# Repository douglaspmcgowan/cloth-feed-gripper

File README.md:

# Cloth-feed gripper site

Public site for the cloth-feed gripper, a UC Berkeley ME102B design that has not been built. It has a landing page, the film, and the interactive design review app. Everything is static and served from `public/`.

## What is in `public/`

| Path | Source |
|---|---|
| `index.html`, `landing.css`, `landing.js`, `favicon.svg` | hand-written, no framework or build |
| `review/index.html` | the review app, wrapped in a document head and a Home link; generated |
| `media/` | teaser, full film, vertical cut, posters and the social image; generated |
| `licenses/` | licence texts for the third-party assets; generated |
| `facts.json`, `tokens.css`, `provenance.json` | figures, design tokens and file hashes read from the source; generated |

`scripts/sync.py` writes every generated file from the source repository at one commit. `provenance.json` records the source repository name, that commit, the sync date, and each served file's public path, sha256 and size; it says nothing about the source repository's layout. The landing page shows no figure that is not read from `facts.json`.

## Commands

```powershell
npm ci
npx playwright install chromium

python scripts/sync.py --ref 996dce6      # refresh generated files; running it twice changes nothing
python scripts/check_public.py            # scan public/ for private content
npm run serve                             # http://127.0.0.1:4173/
npm test                                  # Playwright, 3 sizes x light and dark
npm run lint
```

The moved CAD, analysis, electronics and firmware checks use Python 3.12 and the
dependencies in `requirements-dev.txt`. For example, run
`uv run --python 3.12 --no-project --with-requirements requirements-dev.txt python -m pytest -q cad/gripper analysis/gripper docs/gripper/test ecad/gripper firmware/gripper/test`
from this repository's root. Some committed analysis outputs are already stale;
the move does not regenerate their computed values.

`sync.py` reads this repository by default and takes `--source <path to a checkout>` when another checkout is needed. `.sync/state.json` is git-ignored, so the first run in a fresh clone has no record of the last sync and may rebuild every generated file; the result is the same bytes.

## Checks

- `scripts/check_public.py` looks for emails, phones, addresses, student IDs, local paths, credential shapes, names of people, handout-style phrases and paths from the source repository (read from `scripts/sync.py`'s own input table), in every file including the text inside the review app, and for any digit typed into the landing page's text. A hit passes only with a reviewed line in `scripts/public-allowlist.txt` that also states how many times it occurs; a different count fails. `--self-test` plants one hit per rule. A shingle comparison against a course handout runs only with `--handout <file>` and has not been run. Two limits: the source-path rule knows only the paths `sync.py` reads, so the review app's other evidence citations (relative file names in its Sources panels, which point into the private design repository and are kept on purpose) are not counted; and the typed-digit rule covers the landing page's static text, not text a script writes.
- `npm test` covers console errors, sideways scroll, broken text, the hero poster, film playback, the 3D canvas, each landing door, the Home link, and that nothing outside `public/` is served.

## Deploying

`vercel.json` sets `public` as the output directory with no framework and no build command. Deploying is a separate step that needs the owner's say-so.

After a deploy, run the guard against the live address:

```powershell
npm run check:live -- https://cloth-feed-gripper.vercel.app
```

It prints one line per path and ends with `check_live: N ok, M failed`. It exits non-zero unless the landing page, `/review/`, `/facts.json`, the full film (HEAD) and a licence text return 200, the landing page carries its title and `/facts.json` parses with a requirement count, and every path in its hidden list returns 404. The hidden list is in `scripts/check_live.mjs`: repository files outside `public/` (contract, task and spec files, `package.json`, `vercel.json`, `.git/config`, `.sync/state.json`, the scripts, the allowlist, a test, `node_modules`) and `public/`-prefixed copies of served files.

## Runtime dependencies

The review app loads three.js from jsDelivr, and both pages load Public Sans from Google Fonts. Without a network the 3D views do not draw.

## Credits

See the credits section of the landing page: SO-ARM100 geometry (Apache-2.0), Archivo and Public Sans (OFL), three.js (MIT).

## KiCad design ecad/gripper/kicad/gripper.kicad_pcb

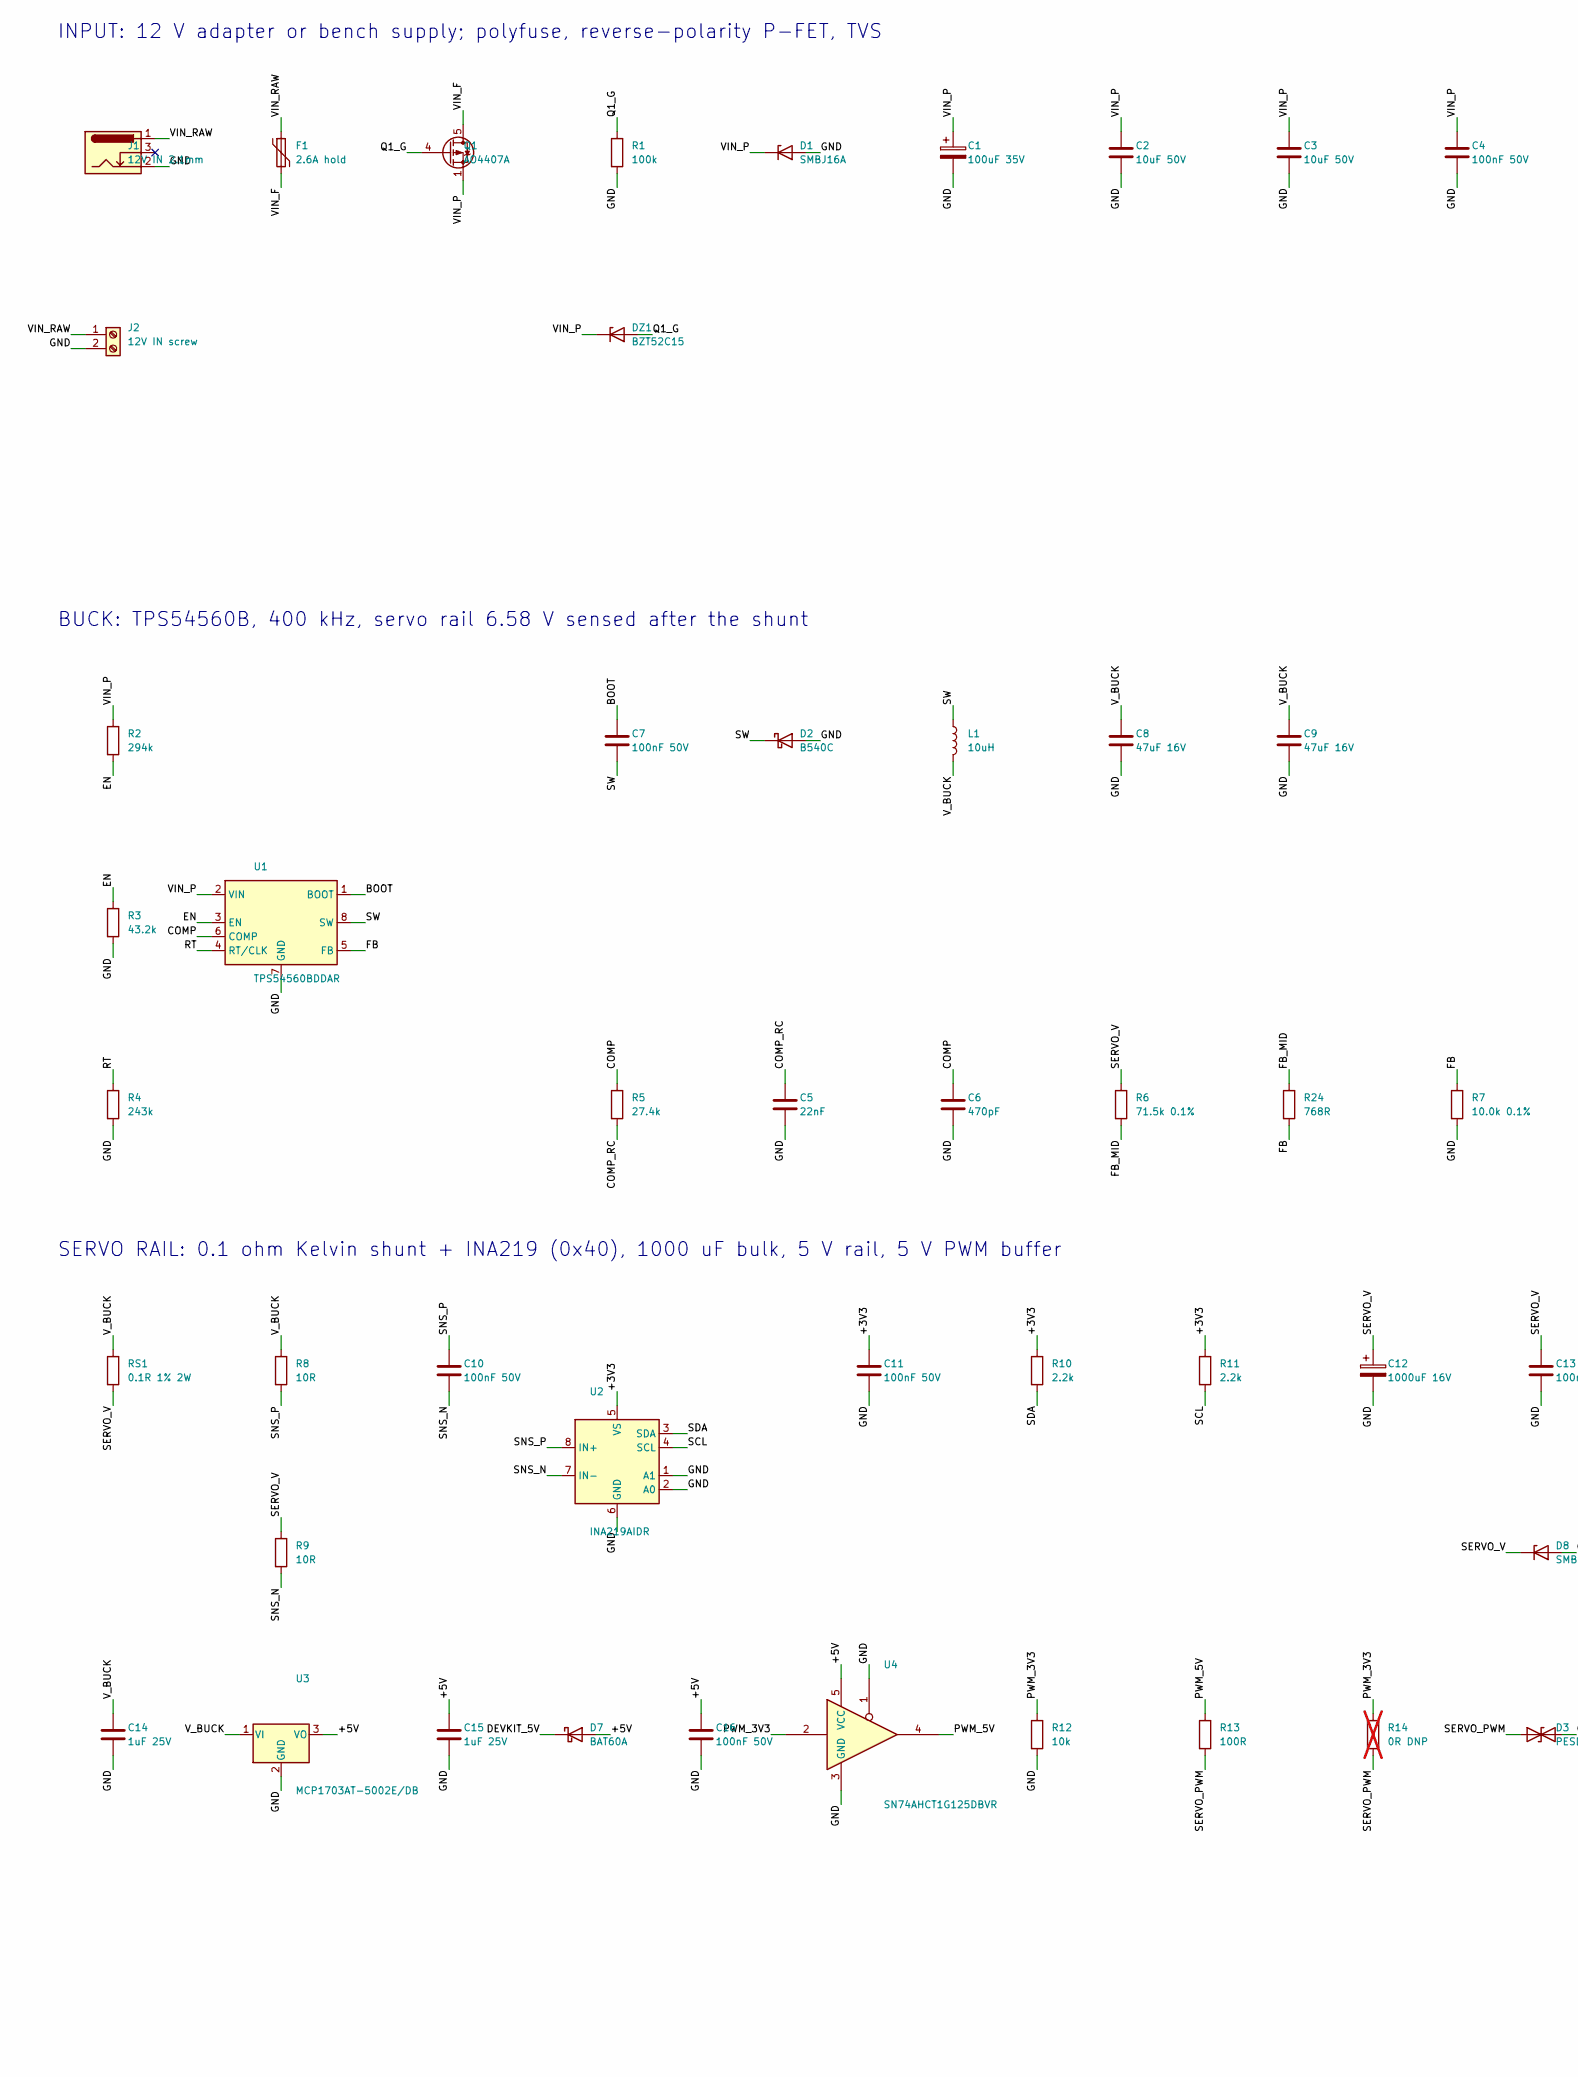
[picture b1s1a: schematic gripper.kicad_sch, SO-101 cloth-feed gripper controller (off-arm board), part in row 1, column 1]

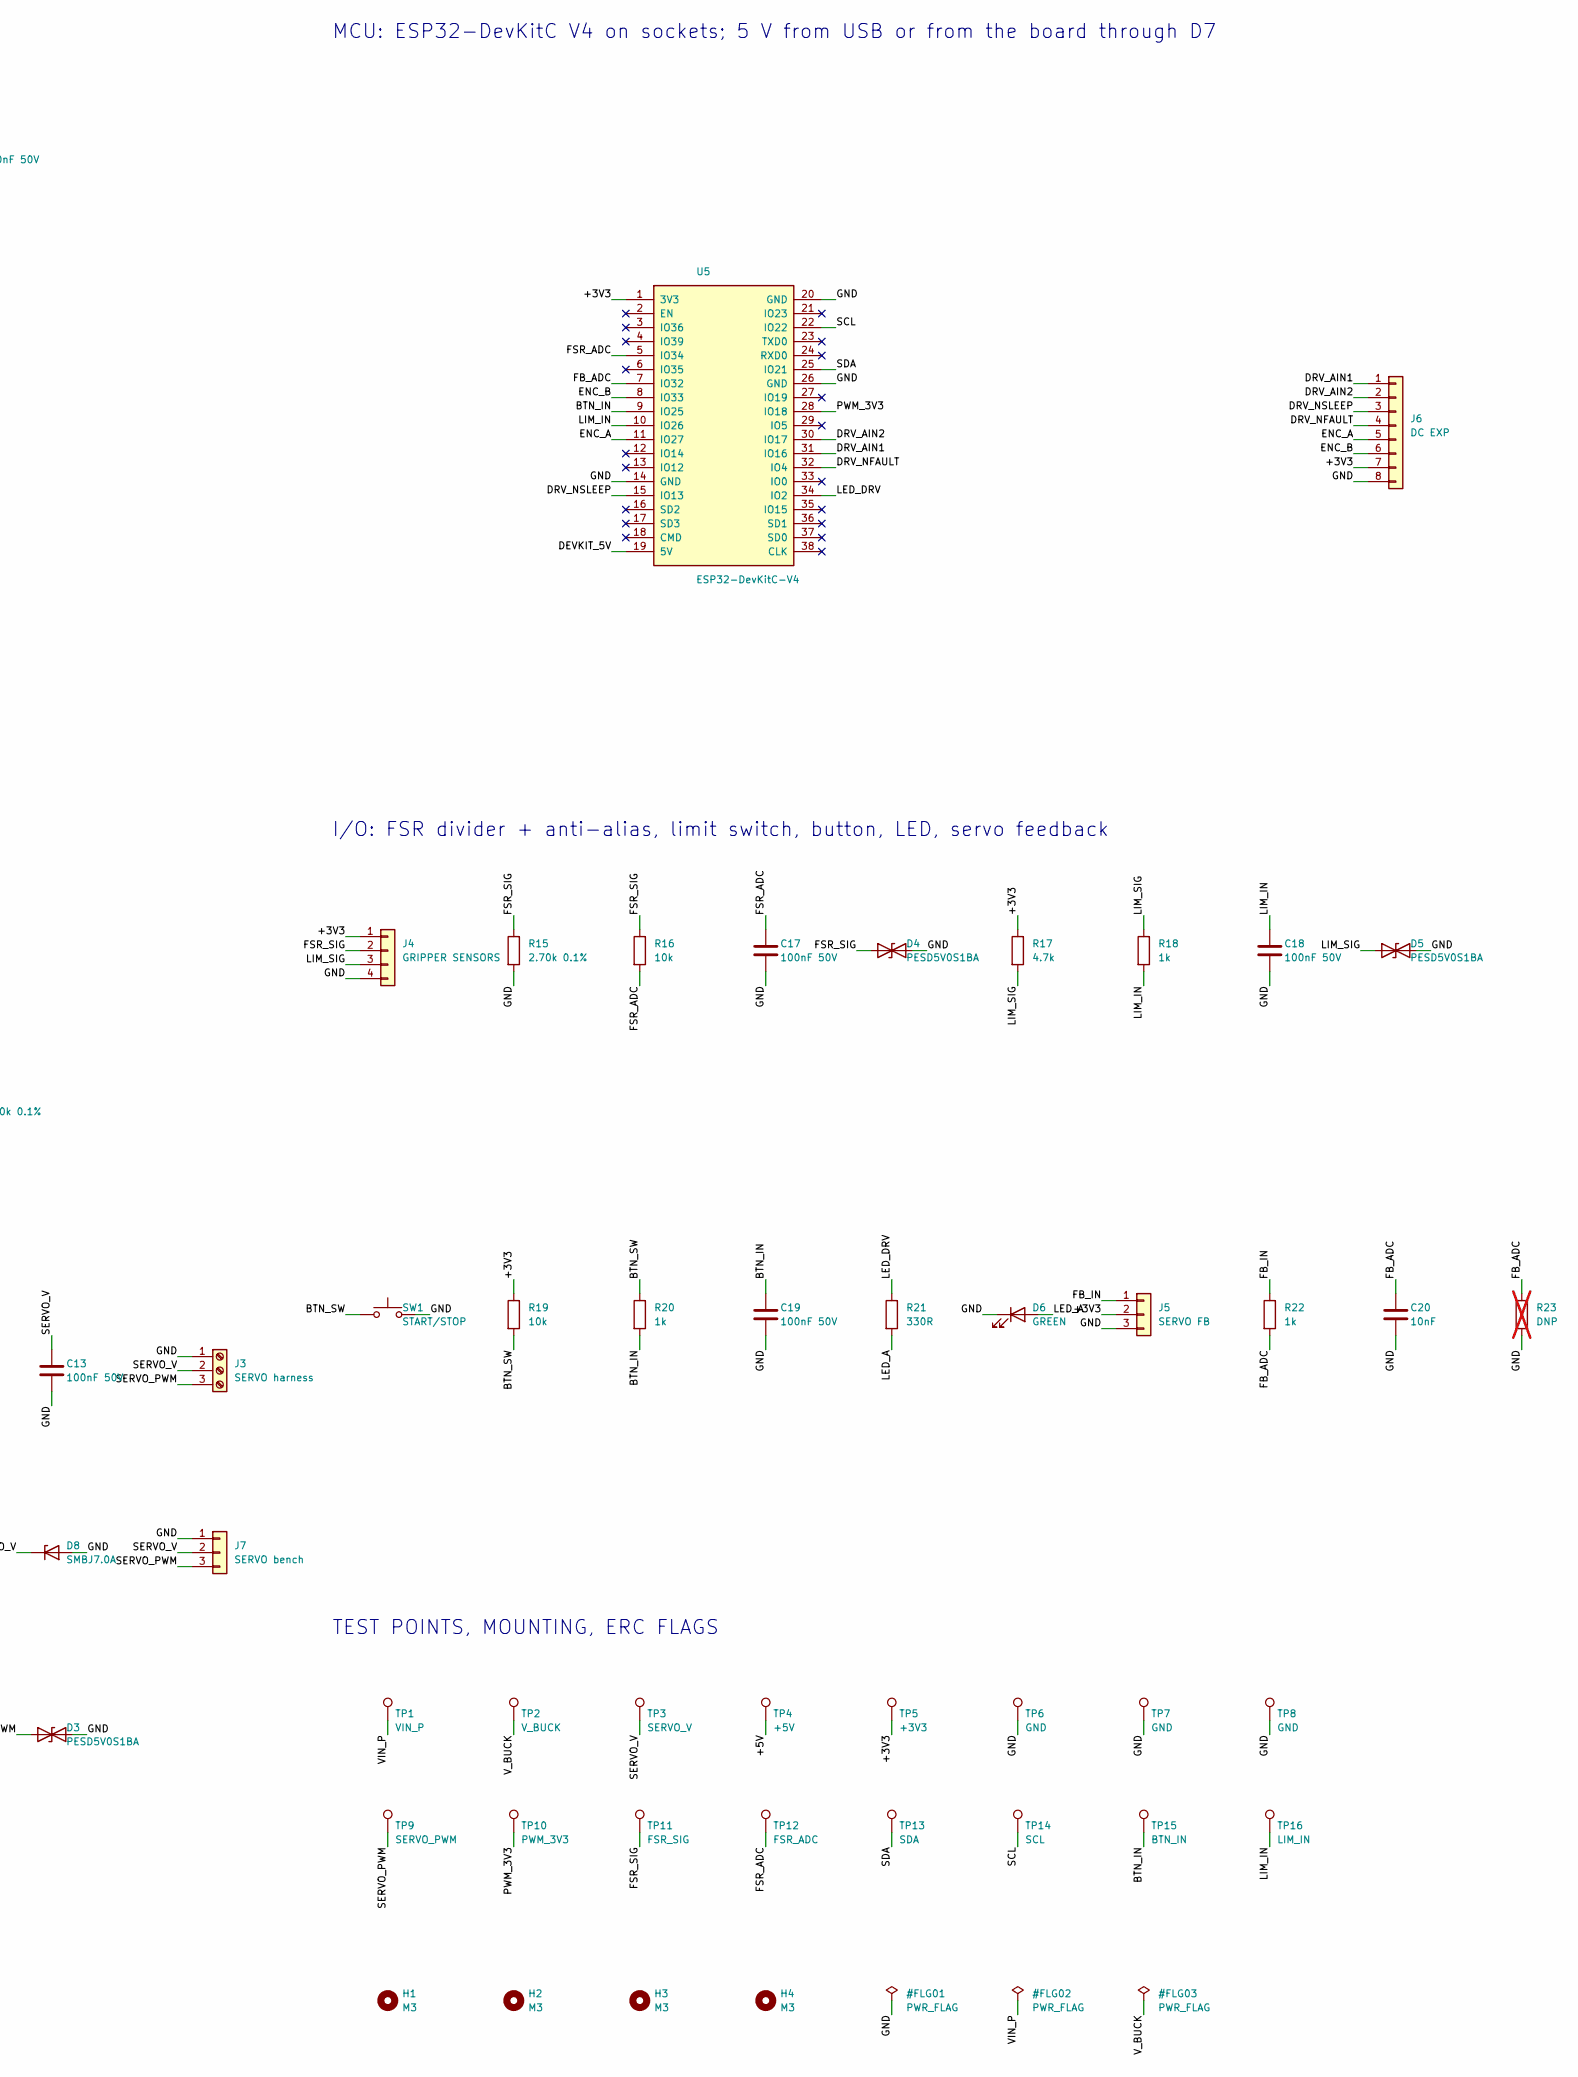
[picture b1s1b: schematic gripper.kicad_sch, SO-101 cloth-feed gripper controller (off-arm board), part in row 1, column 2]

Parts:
C1: 100uF 35V; CP_Radial_D8.0mm_P3.50mm; MPN EEU-FR1V101
C2, C3: 10uF 50V; C_1210_3225Metric; MPN GRM32ER71H106KA12L; LCSC Part # C77102
C4, C7, C10, C11, C13, C16, C17, C18, C19: 100nF 50V; C_0603_1608Metric; MPN CC0603KRX7R9BB104; LCSC Part # C14663
C5: 22nF; C_0603_1608Metric; MPN CL10B223KB8NNNC; LCSC Part # C21122
C6: 470pF; C_0603_1608Metric; MPN CL10C471JB8NNNC; LCSC Part # C27694
C8, C9: 47uF 16V; C_1210_3225Metric; MPN CL32A476KOJNNWE; LCSC Part # C730498
C12: 1000uF 16V; CP_Radial_D10.0mm_P5.00mm; MPN EEU-FR1C102B
C14, C15: 1uF 25V; C_0603_1608Metric; MPN CL10A105KB8NNNC; LCSC Part # C15849
C20: 10nF; C_0603_1608Metric; MPN CL10B103KB8NNNC; LCSC Part # C1589
D1: SMBJ16A; D_SMB; MPN SMBJ16A-M3/52; LCSC Part # C1979375
D2: B540C; D_SMC; MPN B540C-13-F; LCSC Part # C72264
D3, D4, D5: PESD5V0S1BA; D_SOD-323; MPN PESD5V0S1BA,115; LCSC Part # C19224
D6: GREEN; LED_0805_2012Metric; MPN TJ-S2012SW8TGLC2G-A5; LCSC Part # C192319
D7: BAT60A; D_SOD-323; MPN BAT60AE6327HTSA1
D8: SMBJ7.0A; D_SMB; MPN SMBJ7.0A
DZ1: BZT52C15; D_SOD-123; MPN BZT52C15; LCSC Part # C2104
F1: 2.6A hold; Fuse_1812_4532Metric; MPN SMD1812P260TF/16; LCSC Part # C20814
H1, H2, H3, H4: M3; MountingHole_3.2mm_M3
J1: 12V IN 2.1mm; BarrelJack_CUI_PJ-102AH_Horizontal; MPN PJ-102AH
J2: 12V IN screw; TerminalBlock_Phoenix_MKDS-1,5-2-5.08_1x02_P5.08mm_Horizont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; MPN 1715721
J3: SERVO harness; TerminalBlock_Phoenix_MKDS-1,5-3-5.08_1x03_P5.08mm_Horizont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; MPN 1715734
J4: GRIPPER SENSORS; JST_XH_B4B-XH-A_1x04_P2.50mm_Vertical; MPN B4B-XH-A(LF)(SN); LCSC Part # C144395
J5: SERVO FB; PinHeader_1x03_P2.54mm_Vertical; MPN Break-away 0.1 in 36-pin male header (1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
J6: DC EXP; PinHeader_1x08_P2.54mm_Vertical; MPN Break-away 0.1 in 36-pin male header (1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
J7: SERVO bench; PinHeader_1x03_P2.54mm_Vertical; MPN Break-away 0.1 in 36-pin male header (1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
L1: 10uH; L_Bourns_SRP1245A; MPN SRP1245A-100M
Q1: AO4407A; SOIC-8_3.9x4.9mm_P1.27mm; MPN AO4407A; LCSC Part # C7379957
R1: 100k; R_0603_1608Metric; MPN 0603WAF1003T5E; LCSC Part # C25803
R2: 294k; R_0603_1608Metric; MPN CRCW0603294KFKEA; LCSC Part # C2092132
R3: 43.2k; R_0603_1608Metric; MPN RC0603FR-0743K2L
R4: 243k; R_0603_1608Metric; MPN RC0603FR-07243KL; LCSC Part # C137764
R5: 27.4k; R_0603_1608Metric; MPN CRCW060327K4FKEA; LCSC Part # C843937
R6: 71.5k 0.1%; R_0603_1608Metric; MPN RT0603BRD0771K5L
R7: 10.0k 0.1%; R_0603_1608Metric; MPN RT0603BRD0710KL
R8, R9: 10R; R_0603_1608Metric; MPN 0603WAF100JT5E; LCSC Part # C22859
R10, R11: 2.2k; R_0603_1608Metric; MPN 0603WAF2201T5E; LCSC Part # C4190
R12, R16, R19: 10k; R_0603_1608Metric; MPN RC0603FR-0710KL; LCSC Part # C98220
R13: 100R; R_0603_1608Metric; MPN 0603WAF1000T5E; LCSC Part # C22775
R14: 0R DNP; R_0603_1608Metric; MPN 0603WAF0000T5E; LCSC Part # C21189; not fitted
R15: 2.70k 0.1%; R_0603_1608Metric; MPN RT0603BRD072K7L
R17: 4.7k; R_0603_1608Metric; MPN 0603WAF4701T5E; LCSC Part # C23162
R18, R20, R22: 1k; R_0603_1608Metric; MPN 0603WAF1001T5E; LCSC Part # C21190
R21: 330R; R_0603_1608Metric; MPN 0603WAF3300T5E; LCSC Part # C23138
R23: DNP; R_0603_1608Metric; MPN 0603WAF0000T5E; LCSC Part # C21189; not fitted
R24: 768R; R_0603_1608Metric; MPN RC0603FR-07768RL
RS1: 0.1R 1% 2W; R_2512_6332Metric; MPN PE2512FKE7W0R1L; LCSC Part # C165698
SW1: START/STOP; SW_PUSH_6mm; MPN Tactile Button switch 6 mm (20-pack)
TP1: VIN_P; TestPoint_Keystone_5000-5004_Miniature; MPN 5000
TP2: V_BUCK; TestPoint_Keystone_5000-5004_Miniature; MPN 5000
TP3: SERVO_V; TestPoint_Keystone_5000-5004_Miniature; MPN 5000
TP4: +5V; TestPoint_Keystone_5000-5004_Miniature; MPN 5000
TP5: +3V3; TestPoint_Keystone_5000-5004_Miniature; MPN 5000
TP6, TP7, TP8: GND; TestPoint_Keystone_5000-5004_Miniature; MPN 5000
TP9: SERVO_PWM; TestPoint_Keystone_5000-5004_Miniature; MPN 5000
TP10: PWM_3V3; TestPoint_Keystone_5000-5004_Miniature; MPN 5000
TP11: FSR_SIG; TestPoint_Keystone_5000-5004_Miniature; MPN 5000
TP12: FSR_ADC; TestPoint_Keystone_5000-5004_Miniature; MPN 5000
TP13: SDA; TestPoint_Keystone_5000-5004_Miniature; MPN 5000
TP14: SCL; TestPoint_Keystone_5000-5004_Miniature; MPN 5000
TP15: BTN_IN; TestPoint_Keystone_5000-5004_Miniature; MPN 5000
TP16: LIM_IN; TestPoint_Keystone_5000-5004_Miniature; MPN 5000
U1: TPS54560BDDAR; Texas_R-PDSO-G8_EP2.95x4.9mm_Mask2.4x3.1mm_ThermalVias; MPN TPS54560BDDAR
U2: INA219AIDR; SOIC-8_3.9x4.9mm_P1.27mm; MPN INA219AIDR; LCSC Part # C138706
U3: MCP1703AT-5002E/DB; SOT-223-3_TabPin2; MPN MCP1703AT-5002E/DB
U4: SN74AHCT1G125DBVR; SOT-23-5; MPN SN74AHCT1G125DBVR; LCSC Part # C7484
U5: ESP32-DevKitC-V4; ESP32-DevKitC-V4_Socket; MPN ESP32-DEVKITC-32E

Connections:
/+3V3: C11.1, J4.1, J5.2, J6.7, R10.1, R11.1, R17.1, R19.1, TP5.1, U2.5 (VS), U5.1 (3V3)
/+5V: C15.1, C16.1, D7.2 (A), TP4.1, U3.3 (VO), U4.5 (VCC)
/BOOT: C7.1, U1.1 (BOOT)
/BTN_IN: C19.1, R20.2, TP15.1, U5.9 (IO25)
/BTN_SW: R19.2, R20.1, SW1.1
/COMP: C6.1, R5.1, U1.6 (COMP)
/COMP_RC: C5.1, R5.2
/DEVKIT_5V: D7.1 (K), U5.19 (5V)
/DRV_AIN1: J6.1, U5.31 (IO16)
/DRV_AIN2: J6.2, U5.30 (IO17)
/DRV_NFAULT: J6.4, U5.32 (IO4)
/DRV_NSLEEP: J6.3, U5.15 (IO13)
/EN: R2.2, R3.1, U1.3 (EN)
/ENC_A: J6.5, U5.11 (IO27)
/ENC_B: J6.6, U5.8 (IO33)
/FB: R7.1, R24.2, U1.5 (FB)
/FB_ADC: C20.1, R22.2, R23.1, U5.7 (IO32)
/FB_IN: J5.1, R22.1
/FB_MID: R6.2, R24.1
/FSR_ADC: C17.1, R16.2, TP12.1, U5.5 (IO34)
/FSR_SIG: D4.1 (A1), J4.2, R15.1, R16.1, TP11.1
/GND: C1.2, C2.2, C3.2, C4.2, C5.2, C6.2, C8.2, C9.2, C11.2, C12.2, C13.2, C14.2, C15.2, C16.2, C17.2, C18.2, C19.2, C20.2, D1.2 (A), D2.2 (A), D3.2 (A2), D4.2 (A2), D5.2 (A2), D6.1 (K), D8.2 (A), J1.2, J2.2, J3.1, J4.4, J5.3, J6.8, J7.1, R1.2, R3.2, R4.2, R7.2, R12.2, R15.2, R23.2, SW1.2, TP6.1, TP7.1, TP8.1, U1.7 (GND), U1.9 (GND), U2.1 (A1), U2.2 (A0), U2.6 (GND), U3.2 (GND), U4.1, U4.3 (GND), U5.14 (GND), U5.20 (GND), U5.26 (GND)
/LED_A: D6.2 (A), R21.2
/LED_DRV: R21.1, U5.34 (IO2)
/LIM_IN: C18.1, R18.2, TP16.1, U5.10 (IO26)
/LIM_SIG: D5.1 (A1), J4.3, R17.2, R18.1
/PWM_3V3: R12.1, R14.1, TP10.1, U4.2, U5.28 (IO18)
/PWM_5V: R13.1, U4.4
/Q1_G: DZ1.2 (A), Q1.4 (G), R1.1
/RT: R4.1, U1.4 (RT/CLK)
/SCL: R11.2, TP14.1, U2.4 (SCL), U5.22 (IO22)
/SDA: R10.2, TP13.1, U2.3 (SDA), U5.25 (IO21)
/SERVO_PWM: D3.1 (A1), J3.3, J7.3, R13.2, R14.2, TP9.1
/SERVO_V: C12.1, C13.1, D8.1 (K), J3.2, J7.2, R6.1, R9.1, RS1.2, TP3.1
/SNS_N: C10.2, R9.2, U2.7 (IN-)
/SNS_P: C10.1, R8.2, U2.8 (IN+)
/SW: C7.2, D2.1 (K), L1.1, U1.8 (SW)
/VIN_F: F1.2, Q1.5 (D), Q1.6 (D), Q1.7 (D), Q1.8 (D)
/VIN_P: C1.1, C2.1, C3.1, C4.1, D1.1 (K), DZ1.1 (K), Q1.1 (S), Q1.2 (S), Q1.3 (S), R2.1, TP1.1, U1.2 (VIN)
/VIN_RAW: F1.1, J1.1, J2.1
/V_BUCK: C8.1, C9.1, C14.1, L1.2, R8.1, RS1.1, TP2.1, U3.1 (VI)

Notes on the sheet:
INPUT: 12 V adapter or bench supply; polyfuse, reverse-polarity P-FET, TVS
BUCK: TPS54560B, 400 kHz, servo rail 6.58 V sensed after the shunt
SERVO RAIL: 0.1 ohm Kelvin shunt + INA219 (0x40), 1000 uF bulk, 5 V rail, 5 V PWM buffer
MCU: ESP32-DevKitC V4 on sockets; 5 V from USB or from the board through D7
I/O: FSR divider + anti-alias, limit switch, button, LED, servo feedback
TEST POINTS, MOUNTING, ERC FLAGS

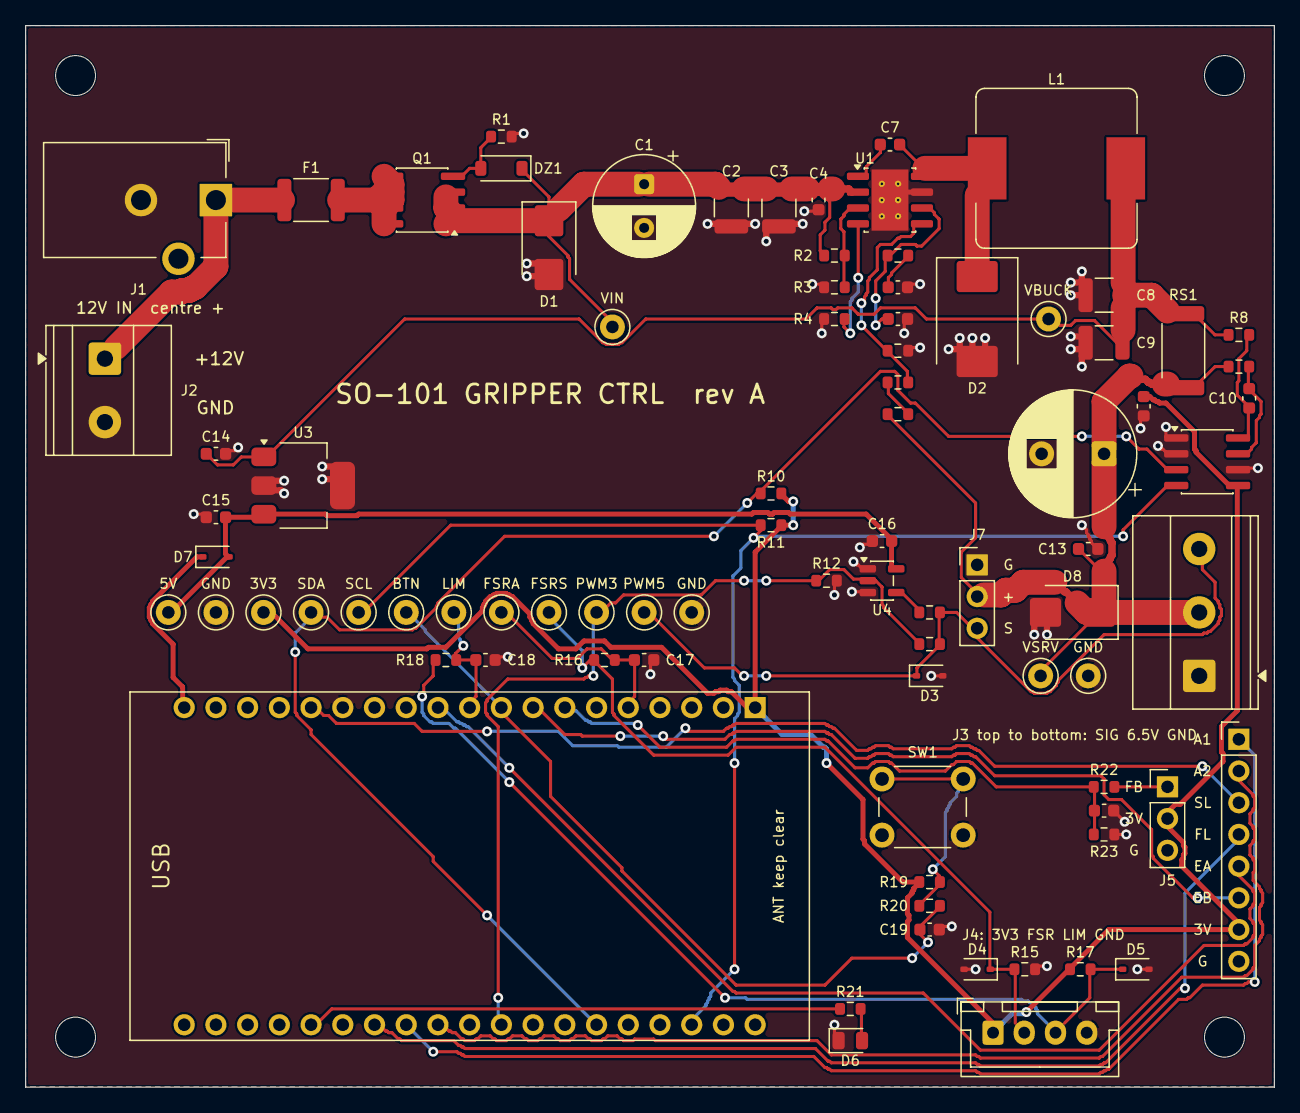
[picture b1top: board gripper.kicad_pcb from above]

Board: 2 copper layers, 100.0 x 85.0 mm, 90 parts (0 on the bottom side), 41 nets.

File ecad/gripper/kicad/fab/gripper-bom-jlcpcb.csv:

Comment,Designator,Footprint,LCSC Part #
10uF 50V,"C2,C3",C_1210_3225Metric,C77102
100nF 50V,"C4,C7,C10,C11,C13,C16,C17,C18,C19",C_0603_1608Metric,C14663
22nF,C5,C_0603_1608Metric,C21122
470pF,C6,C_0603_1608Metric,C27694
47uF 16V,"C8,C9",C_1210_3225Metric,C730498
1uF 25V,"C14,C15",C_0603_1608Metric,C15849
10nF,C20,C_0603_1608Metric,C1589
SMBJ16A,D1,D_SMB,C1979375
B540C,D2,D_SMC,C72264
PESD5V0S1BA,"D3,D4,D5",D_SOD-323,C19224
GREEN,D6,LED_0805_2012Metric,C192319
BZT52C15,DZ1,D_SOD-123,C2104
2.6A hold,F1,Fuse_1812_4532Metric,C20814
GRIPPER SENSORS,J4,JST_XH_B4B-XH-A_1x04_P2.50mm_Vertical,C144395
AO4407A,Q1,SOIC-8_3.9x4.9mm_P1.27mm,C7379957
100k,R1,R_0603_1608Metric,C25803
294k,R2,R_0603_1608Metric,C2092132
243k,R4,R_0603_1608Metric,C137764
27.4k,R5,R_0603_1608Metric,C843937
10R,"R8,R9",R_0603_1608Metric,C22859
2.2k,"R10,R11",R_0603_1608Metric,C4190
10k,"R12,R16,R19",R_0603_1608Metric,C98220
100R,R13,R_0603_1608Metric,C22775
4.7k,R17,R_0603_1608Metric,C23162
1k,"R18,R20,R22",R_0603_1608Metric,C21190
330R,R21,R_0603_1608Metric,C23138
0.1R 1% 2W,RS1,R_2512_6332Metric,C165698
INA219AIDR,U2,SOIC-8_3.9x4.9mm_P1.27mm,C138706
SN74AHCT1G125DBVR,U4,SOT-23-5,C7484

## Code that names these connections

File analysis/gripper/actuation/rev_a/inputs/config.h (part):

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// Board: ESP32 DevKitC (ESP32-WROOM-32, classic ESP32), FQBN esp32:esp32:esp32, core 2.0.17 [DB D6, A].
// Analog inputs on ADC1 only: ADC2 is unavailable while Wi-Fi runs [S: ESP-IDF ADC docs].
// ---------------------------------------------------------------------------
#define PIN_SERVO_PWM        18   // servo signal, 3.3 V logic (M16: add 74AHCT125 if the servo ignores it) [DB]
#define PIN_FSR_ADC          34   // ADC1_CH6, input-only; FSR divider node [DB]
#define PIN_SERVO_FB_ADC     32   // ADC1_CH4; optional servo pot tap (DS3218MG has no 4th wire) [DB]
#define PIN_BUTTON           25   // START/STOP momentary to GND, INPUT_PULLUP [DB]
#define PIN_LIMIT_OPEN       26   // jaw-open limit switch to GND, INPUT_PULLUP [DB]
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// compile error (gripper.ino). Its pins and constants below are kept for that future branch only.
// #define ACTUATOR_DC_GEARMOTOR

#define PIN_DRV_AIN1         16   // DRV8833 AIN1 (PWM)                 [DC branch, A]
#define PIN_DRV_AIN2         17   // DRV8833 AIN2 (PWM)                 [DC branch, A]
#define PIN_DRV_NSLEEP       13   // DRV8833 nSLEEP, high = enabled     [DC branch, A]
#define PIN_DRV_NFAULT        4   // DRV8833 nFAULT, open-drain low = fault [DC branch, S: Pololu 2130]
#define PIN_ENC_A            27   // encoder channel A                  [DC branch, A]
#define PIN_ENC_B            33   // encoder channel B                  [DC branch, A]

// Optional peripherals (1 = present). A missing INA219 is detected at boot and disabled, not faulted.
#define INA219_ENABLED       1    // [DB]
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
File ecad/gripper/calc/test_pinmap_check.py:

"""pinmap_check.py: parser, rules, and the repository's own pin map."""
import os

import _common as cm
import design
import pinmap_check as pm


def test_config_h_defines_parse_and_match_design():
    cfg = pm.parse_config()
    assert len(cfg) == len(design.GPIO_NETS) == 14
    assert cfg['PIN_FSR_ADC'] == 34 and cfg['PIN_SERVO_PWM'] == 18
    for gpio, (net, macro) in design.GPIO_NETS.items():
        assert cfg[macro] == gpio


def test_socket_pin_numbers_by_hand():
    # J2 is pins 1-19 (3V3, EN, IO36, IO39, IO34, ...): IO34 is the fifth pin; J3 pin 1 is socket pin 20 (GND)
    assert design.devkit_pin_number(34) == 5
    assert design.devkit_pin_number(32) == 7
    assert design.devkit_pin_number(18) == 28
    assert design.devkit_pin_number(23) == 21


def test_the_repository_pin_map_passes():
    r = pm.run()
    assert all(x['match'] for x in r['lines'])
    assert all(x['ok'] for x in r['socket'])
    assert all(x['ok'] for x in r['rules'])
    assert r['ok'] is True


def test_rules_reject_bad_pins(monkeypatch):
    bad = dict(design.GPIO_NETS)
    bad[12] = ('BTN_IN', 'PIN_BUTTON')           # GPIO 12 is a strapping pin
    del bad[25]
    monkeypatch.setattr(design, 'GPIO_NETS', bad)
    r = pm.run()
    row12 = [x for x in r['rules'] if x['gpio'] == 12][0]
    assert 'strapping' in row12['notes']
    assert not r['ok']                              # config.h says PIN_BUTTON is 25, not 12


def test_netlist_parser_and_matching(tmp_path):
    text = '(export (version "E") (nets (net (code "1") (name "/PWM_3V3") (node (ref "U5") (pin "28")) (node (ref "U4") (pin "2"))) (net (code "2") (name "GND") (node (ref "U5") (pin "1")))))'
    p = tmp_path / 'x.net'
    p.write_text(text, encoding='utf-8', newline='\n')
    pins = pm.netlist_pins(str(p))
    assert pins[('U5', '28')] == '/PWM_3V3' and pins[('U5', '1')] == 'GND'
    assert pm.net_matches('/PWM_3V3', 'PWM_3V3') and not pm.net_matches('GND', 'PWM_3V3')
    assert not pm.net_matches(None, 'X')
